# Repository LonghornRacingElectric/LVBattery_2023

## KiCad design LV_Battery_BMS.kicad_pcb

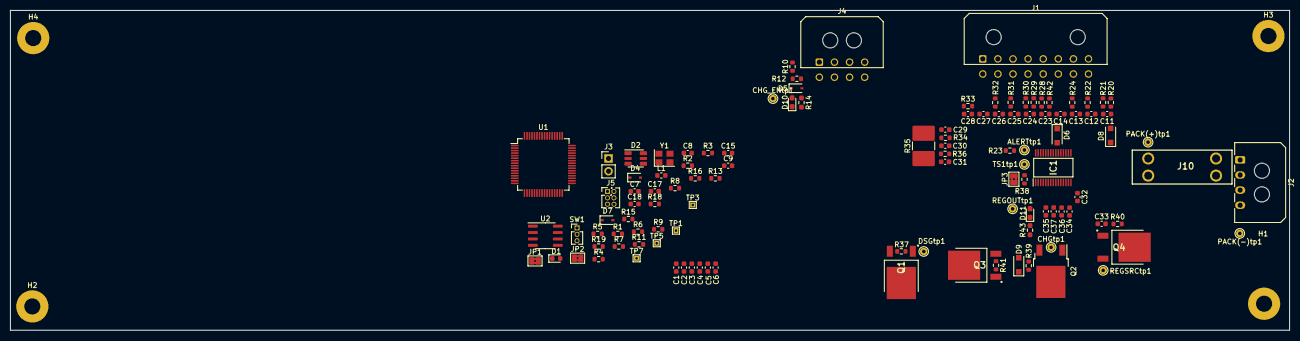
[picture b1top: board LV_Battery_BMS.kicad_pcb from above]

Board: 2 copper layers, 254.0 x 63.5 mm, 116 parts (0 on the bottom side), 71 nets, no tracks yet.

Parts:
ALERTtp1: TestPoint; TestPoint_THTPad_D1.5mm_Drill0.7mm
C1: 4u7; C_0603_1608Metric
C2, C3, C4, C5, C6: 100n; C_0603_1608Metric
C7: 1u; C_0603_1608Metric
C8: 10n; C_0603_1608Metric
C9: 0u1; C_0603_1608Metric
C11, C12, C13, C14, C23, C24, C25, C26, C27, C28, C32, C35, C36: 1uF; C_0603_1608Metric
C15: 4.7n; C_0603_1608Metric
C17, C18: 10p; C_0603_1608Metric
C29, C30, C31: 0.1uF; C_0603_1608Metric
C33, C34: 10uF; C_0603_1608Metric
C37: 4.7uF; C_0603_1608Metric
CHG_ENtp1: TestPoint; TestPoint_THTPad_D1.5mm_Drill0.7mm
CHGtp1: TestPoint; TestPoint_THTPad_D1.5mm_Drill0.7mm
D1: RED; LED_0603_1608Metric
D2: SMLVN6RGB; LED_ROHM_SMLVN6
D4, D5, D7: 3V3; D_SOD-323
D6, D8, D9: 1A; D_SOD-123F
D10: RED; LED_0603_1608Metric_Pad1.05x0.95mm_HandSolder
D11: GREEN; LED_0603_1608Metric_Pad1.05x0.95mm_HandSolder
DSGtp1: TestPoint; TestPoint_THTPad_D1.5mm_Drill0.7mm
H1, H2, H3, H4: MountingHole; MountingHole_3.2mm_M3_Pad
IC1: BQ7693007DBTR; SOP50P640X120-30N
J1: Conn_02x08_Odd_Even; Molex_Micro-Fit_3.0_43045-1600_2x08_P3.00mm_Horizontal
J2: Conn_01x04; Molex_Micro-Fit_3.0_43650-0400_1x04_P3.00mm_Horizontal
J3: Conn_01x02; PinHeader_1x02_P2.54mm_Vertical
J4: Conn_01x08; Molex_Micro-Fit_3.0_43045-0800_2x04_P3.00mm_Horizontal
J5: SWD; PinHeader_2x03_P1.27mm_Vertical
J10: 3557-2
JP1, JP2, JP3: SolderJumper-2_P1.3mm_Bridged2Bar_Pad1.0x1.5mm
L1: 68n; L_0603_1608Metric
PACK(+)tp1: TestPoint; TestPoint_THTPad_D1.5mm_Drill0.7mm
PACK(-)tp1: TestPoint; TestPoint_THTPad_D1.5mm_Drill0.7mm
Q1, Q3, Q4: Q_NMOS_GSD; PG-TO-252
Q2: Q_PMOS_DGS; TO-252-2
R1, R2, R3, R4: 2k2; R_0603_1608Metric
R5, R34, R36, R40, R42: 100; R_0603_1608Metric
R6, R7, R8: 220; R_0603_1608Metric
R9, R11, R13, R16: 120; R_0603_1608Metric
R10: 2.3k; R_0603_1608Metric
R12: 270; R_0603_1608Metric
R14, R43: 470R; R_0603_1608Metric_Pad0.98x0.95mm_HandSolder
R15: 47; R_0603_1608Metric
R18: 10K; R_0603_1608Metric
R19: 22; R_0603_1608Metric
R20, R21, R22, R24, R28, R29, R30, R31, R32, R33: 1k; R_0603_1608Metric
R23, R37, R39, R41: 1M; R_0603_1608Metric
R35: 8mOhm; R_2816_7142Metric
R38: 10k; R_0603_1608Metric
REGOUTtp1: TestPoint; TestPoint_THTPad_D1.5mm_Drill0.7mm
REGSRCtp1: TestPoint; TestPoint_THTPad_D1.5mm_Drill0.7mm
SW1: SW_SPDT; PinHeader_1x03_P1.27mm_Vertical
TP1, TP3, TP5, TP7: TestPoint_THTPad_1.0x1.0mm_Drill0.5mm
TS1tp1: TestPoint; TestPoint_THTPad_D1.5mm_Drill0.7mm
U1: STM32F105RCTx; LQFP-64_10x10mm_P0.5mm
U2: SN65HVD230; SOIC-8_3.9x4.9mm_P1.27mm
Y1: 16MHz; Crystal_SMD_3225-4Pin_3.2x2.5mm

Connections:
+3.3VA: C7.1, C8.1, L1.2, U1.13 (VDDA)
+3V3: C1.1, C2.1, C3.1, C4.1, C5.1, C6.1, C9.1, C37.1, D1.2 (A), D2.1 (BA), D2.2 (RA), D2.3 (GA), D11.2 (A), IC1.8 (REGOUT), J5.1, L1.1, R1.1, R2.1, R3.1, R4.1, REGOUTtp1.1, SW1.1 (A), U1.1 (VBAT), U1.19 (VDD), U1.32 (VDD), U1.48 (VDD), U1.64 (VDD), U2.3 (VCC)
+24V: J1.15, J10.2, J10.4, PACK(+)tp1.1, Q4.3 (D), R20.1, R40.2
/ALERT_OUT: ALERTtp1.1, IC1.30 (ALERT), R23.1, U1.39 (PC8)
/CAN_H: J4.3, JP1.2 (B)
/CAN_L: J4.4, JP2.2 (B)
/CHG_EN: CHG_ENtp1.1, D5.1 (K), D10.2 (A), R10.1, R12.2, U1.40 (PC9)
/CLK: IC1.5 (SCL), R1.2, U1.58 (PB6)
/Cell1(+): J1.1, J1.4, R32.1
/Cell2(+): J1.3, J1.6, R31.1
/Cell3(+): J1.5, J1.8, R30.1
/Cell4(+): J1.7, J1.10, R28.1, R29.1, R42.2
/Cell5(+): J1.9, J1.12, R24.1
/Cell6(+): J1.11, J1.14, R22.1
/Cell7(+): J1.13, J1.16, R21.1
/DATA: IC1.4 (SDA), R2.2, U1.59 (PB7)
/Microcontroller/BOOT0: R18.2, U1.60 (BOOT0)
/Microcontroller/CAN1_RX: TP3.1, U1.61 (PB8), U2.4 (R)
/Microcontroller/CAN1_TX: TP1.1, U1.62 (PB9), U2.1 (D)
/Microcontroller/HSE_in: C17.1, U1.5 (PD0), Y1.1
/Microcontroller/HSE_out: R15.1, U1.6 (PD1)
/Microcontroller/I2C2_SCL: R3.2, U1.29 (PB10)
/Microcontroller/I2C2_SDA: R4.2, U1.30 (PB11)
/Microcontroller/LED_B: R6.2, U1.16 (PA2)
/Microcontroller/LED_G: R7.2, U1.15 (PA1)
/Microcontroller/LED_R: R8.2, U1.14 (PA0)
/Microcontroller/SWCLK: J5.4, U1.49 (PA14)
/Microcontroller/SWDIO: R19.2, U1.46 (PA13)
/TS1 (+): IC1.6 (TS1), J4.8, R38.1, TS1tp1.1
/TS2 (+): IC1.13 (TS2), J4.6
/TS2 (-): C14.2, C23.1, C32.2, C33.2, C34.1, D6.1 (K), IC1.10 (VC5X), J4.5, Q4.1 (G), R42.1
GND: C1.2, C2.2, C3.2, C4.2, C5.2, C6.2, C7.2, C8.2, C9.2, C15.1, C17.2, C18.2, C27.2, C28.1, C29.1, C31.2, C34.2, C35.2, C36.2, C37.2, D4.2 (A), D5.2 (A), D7.2 (A), IC1.3 (VSS), J1.2, J2.3, J2.4, J4.7, J5.5, PACK(-)tp1.1, Q2.2 (G), Q3.2 (S), R5.2, R12.1, R14.1, R23.2, R33.2, R34.2, R35.2, R41.1, R43.1, SW1.3 (C), U1.12 (VSSA), U1.18 (VSS), U1.31 (VSS), U1.47 (VSS), U1.63 (VSS), U2.2 (GND), U2.8 (Rs), Y1.2, Y1.4
unnamed: C11.1, D8.2 (A), IC1.16 (VC10), R20.2
unnamed: C11.2, C12.1, IC1.17 (VC9), IC1.18 (VC8), R21.2
unnamed: C12.2, C13.1, IC1.19 (VC7), R22.2
unnamed: C13.2, C14.1, IC1.20 (VC6), R24.2
unnamed: C15.2, J3.1, R9.1, R11.1
unnamed: C18.1, R15.2, Y1.3
unnamed: C23.2, IC1.21 (VC5B), R28.2
unnamed: C24.1, D6.2 (A), IC1.22 (VC5), R29.2
unnamed: C24.2, C25.1, IC1.23 (VC4), R30.2
unnamed: C25.2, C26.1, IC1.24 (VC3), IC1.25 (VC2), R31.2
unnamed: C26.2, C27.1, IC1.26 (VC1), JP3.2 (B), R32.2
unnamed: C28.2, IC1.27 (VC0), R33.1
unnamed: C29.2, C30.1, IC1.28 (SRP), R34.1
unnamed: C30.2, C31.1, IC1.29 (SRN), R36.2
unnamed: C32.1, IC1.11 (NC_1), IC1.12 (NC_2), IC1.14 (CAP2)
unnamed: C33.1, D8.1 (K), IC1.15 (BAT), R40.1
unnamed: C35.1, IC1.7 (CAP1)
unnamed: C36.1, IC1.9 (REGSRC), Q4.2 (S), REGSRCtp1.1
unnamed: CHGtp1.1, IC1.2 (CHG), Q2.3 (S)
unnamed: D1.1 (K), R5.1
unnamed: D2.4 (GK), R8.1
unnamed: D2.5 (RK), R7.1
unnamed: D2.6 (BK), R6.1
unnamed: D4.1 (K), JP2.1 (A), R9.2, R11.2, TP7.1, U2.6 (CANL)
unnamed: D7.1 (K), JP1.1 (A), R13.1, R16.1, TP5.1, U2.7 (CANH)
unnamed: D9.1 (K), Q3.1 (G), R39.2, R41.2
unnamed: D9.2 (A), Q2.1 (D), R39.1
unnamed: D10.1 (K), R14.2
unnamed: D11.1 (K), R43.2
unnamed: DSGtp1.1, IC1.1 (DSG), Q1.1 (G), R37.1
unnamed: J2.1, J10.3
unnamed: J2.2, J10.1
unnamed: J3.2, R13.2, R16.2
unnamed: J4.2, R10.2
unnamed: J5.2, R19.1
unnamed: JP3.1 (A), R38.2
unnamed: Q1.2 (S), R35.1, R36.1, R37.2
unnamed: Q1.3 (D), Q3.3 (D)
unnamed: R18.1, SW1.2 (B)

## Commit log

2022-09-26 Added 2023KicadLibrary
2022-11-14 first commit for LV Battery BMS
2023-01-08 added uC, switch to BQ76930
